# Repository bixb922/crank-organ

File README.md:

# MIDI based crank organ software and hardware

# Contents
1.  [Overview](#1-overview)
     * [How is this solution used?](#how-is-this-solution-used)
2.  [Detailed description of software and hardware, schematics, plans](#2-detailed-description-of-software-and-hardware-schematics-plans)
3.  [To see a demo](#3-to-see-a-demo)
4.  [Folders](#4-folders)
5.  [License](#5-license)
6.  [Disclaimer](#6-disclaimer)
7.  [Feedback](#7-feedback)
# 1. Overview

This animation shows how a crank organ with MIDI control works:

The crank moves the bellows. The air is pumped into a reservoir, which connects to the windchest with the pipes. A single pipe is shown, but usually a crank organ has anywhere between 15 and 100 or more pipes. Under the foot of the pipe is a electromagnetical valve (a solenoid valve). The microcontroller stores MIDI files that have the exact time each note starts and stops, and energizes the solenoid (electromagnet) through a driver (a electrical current amplifier). The solenoid opens the airflow at the foot of the pipe, air enters the pipe and vibrates, producing sound. 

Here you can see my homemade crank organ: https://www.youtube.com/@bixb922. This crank organ gave origin to the electronics and software solution in this repository. The organ has 48 pipes: 35 bourdon pipes and 13 piccolo pipes. It has a crank sensor, microphone for tuning and a touch button. It has 4 electronic registers and a button to change the playback speed. Currently I have about 500 MIDI files in the organ.

This repository has a complete hardware and software solution for these devices of mechanical music. This diagram shows how this system works:

The microcontroller stores the MIDI files with the tunes and also has a web server for the cell phone (or a tablet, or PC). On the cell phone a browser such as Chrome or Firefox is used to select the MIDI files that are going to be played. Once a setlist or a tune have been selected, the microcontroller plays the files.

Please note that you really don't need a cell phone or tablet to perform: If you define a setlist, you just turn on the microcontroller and start going. You'll only need a cell phone during performance if you want to change the order of the setlist.

No special application is needed on the cell phone. Just a standard web browser like Firefox or Chrome.

The microcontroller used is a ESP32-S3. Typical boards have about 26 pins available to manage pipes and peripherals, simplifying enormously the electronics for a 20 note organ. It also manages touch pads, counters/encoders, has lots of RAM and flash at a very low battery load, so I think it is a good choice for a microcontroller.  With the available I2C capabilities, the ESP32-S3 could manage many (hundreds?) of pipes.

The repository describes the complete solution:
* hardware schematics
* list of materials
* instructions on how to build the hardware
* complete software (open source) written in a high level language: MicroPython
* a easy installation procedure for the software (no programming skills necessary)
* ready to use configuration files for common crank organ setups

There are many places on internet to describe how to build a crank organ, how to design and cut the pipes, make bellows, windchests, etc.  That description is not part of this repository. However, I included a list of interesting links and some notes on building a MIDI crank organ here: [Buildng a crank organ](building/README.md).

Please post an github issue for any question you might have. Please star this repository if you like what you have seen.

## How is this solution used?

Once the hardware is built (see hardware plans in the doc-hardware folder), install the software, and copy your MIDI files to the microcontroller via WiFi or USB (See software documentation for detailed instructions). You can add more information such as title, genre and lyrics to the music.

You control the order of the tunes with the cell phone. You select tunes to play by tapping on them on the tunelist page on the cell phone. This is done with a very intuitive and easy to use interface using a common browser like Chrome or Firefox. Everything is done over web pages: select a tune, control setlists, configuration, etc.

There are several ways to select tunes to be played:

The creative mode: Tap on a tune on the tunelist, and turn the crank (or touch and release the touchpad) and the tune plays. Then select the next tune, etc. You stay on the tunelist page.

The very creative mode: You can tap several tunes and queue them to play one after the other.

The diligent mode: Before a performance, you can tap several tunes and organize them into a setlist on the performance page. You save the setlist on flash to be ready for the next performance. When the performance begins, you power on the microcontroller, turn the crank (or touch and release the touchpad) and the setlist plays. No need to pull out the cell phone or to push buttons.

The diligent and flexible mode: You can modify the setlist on the fly with the performance page. You can delete or skip a tune, reorder tunes, or select a new tune and move to the top of the list, according to the audience and your wishes.

The very lazy mode: Don't use your cell phone. Don't define a setlist. Turn the microcontroller on. Turn the crank or touch the touchpad. All available tunes will be shuffled randomly and played. 

# 2. Detailed description of software and hardware, schematics, plans
Main documents:

* [Description of the controller software.](doc-software/README.md)
* [Description of the controller hardware and construction plans](doc-hardware/README.md)
* [Building a crank organ](/building/README.md)

Specific documents:
* [Battery](doc-hardware/battery.md). Describes  options for a battery for a crank organ.
* [Crank sensor](doc-hardware/crank-sensor.md) with a summary [here](doc-hardware/README.md#9-crank-rotation-sensor). Describes several options to build or install a crank rotation sensor. This sensor is optional.
* [How to connect an ESP32-S3 to MIDI over serial (MIDI over 5 pin DIN plug) ](https://github.com/bixb922/umidiparser/blob/master/midi_over_serial/midi_over_serial.md). This is interesting if you want to connect this solution to a MIDI card over a serial connection (MIDI over 5 pin DIN plug)
* **NEW** [Use of RC servos to move organ valves](/doc-servo/servos.md). 

This is work in progress, but I am actively using this solution on a daily basis, so I feel it is pretty stable. Please post an issue in the "issue" section or start a discussion in this repository for questions or observations.  I'll be happy to correct any problem and will try to help if there is an issue.

# 3. To see a demo
To see this software in operation, see a demo here: https://bixb922.github.io/demo/index.html.

This demo simulates the operation of the software in this repository closely. The pages have some guidance at the beginning. There is no need to install any software on your PC.

# 4. Folders

| Folder     | Contents                             |
|------------|--------------------------------------|
|bin| Compiled binary files of the software for ESP32-S3|
|building | Description and links on how to build a crank organ |
|data| Pinout templates for 20, 26 and 31 note organs |
|design-and-development| Design details and internals | 
|doc-hardware | Description of electronic hardware |
|doc-software | Description of the crank organ software in this repository|
|doc-servos| How to build valves using RC servos |
|kicad|KiCad source files for the electronics|
|src| Full source code in MicroPython language |
|static| Web pages for the microcontroller (HTML, CSS, Javascript)   |
|tools|Some tools used during development of this software |

[Here](doc-software/README.md) is a change log, see section titled "Recent changes".

# 5. License

This material is available under the MIT license:

This license and disclaimer also covers the hardware design documents. The hardware design is part of the software published here.

Copyright (c) 2023 Hermann Paul von Borries

Permission is hereby granted, free of charge, to any person obtaining a copy
of this software and associated documentation files (the "Software"), to deal
in the Software without restriction, including without limitation the rights
to use, copy, modify, merge, publish, distribute, sublicense, and/or sell
copies of the Software, and to permit persons to whom the Software is
furnished to do so, subject to the following conditions:

The above copyright notice and this permission notice shall be included in all
copies or substantial portions of the Software.

THE SOFTWARE AND DESIGN IS PROVIDED "AS IS", WITHOUT WARRANTY OF ANY KIND, EXPRESS OR
IMPLIED, INCLUDING BUT NOT LIMITED TO THE WARRANTIES OF MERCHANTABILITY,
FITNESS FOR A PARTICULAR PURPOSE AND NONINFRINGEMENT. IN NO EVENT SHALL THE
AUTHORS OR COPYRIGHT HOLDERS BE LIABLE FOR ANY CLAIM, DAMAGES OR OTHER
LIABILITY, WHETHER IN AN ACTION OF CONTRACT, TORT OR OTHERWISE, ARISING FROM,
OUT OF OR IN CONNECTION WITH THE SOFTWARE OR THE USE OR OTHER DEALINGS IN THE
SOFTWARE.

# 6. Disclaimer

The information provided here is for general informational purposes only. All information on this repository is provided in good faith, however I make no representation or warranty of any kind, express or implied, regarding the accuracy, adequacy, validity, reliability, availability or completeness of any information in this repository. 

# 7. Feedback

Feedback is welcome. Please post questions, corrections or comments here: https://github.com/bixb922/crank-organ/discussions

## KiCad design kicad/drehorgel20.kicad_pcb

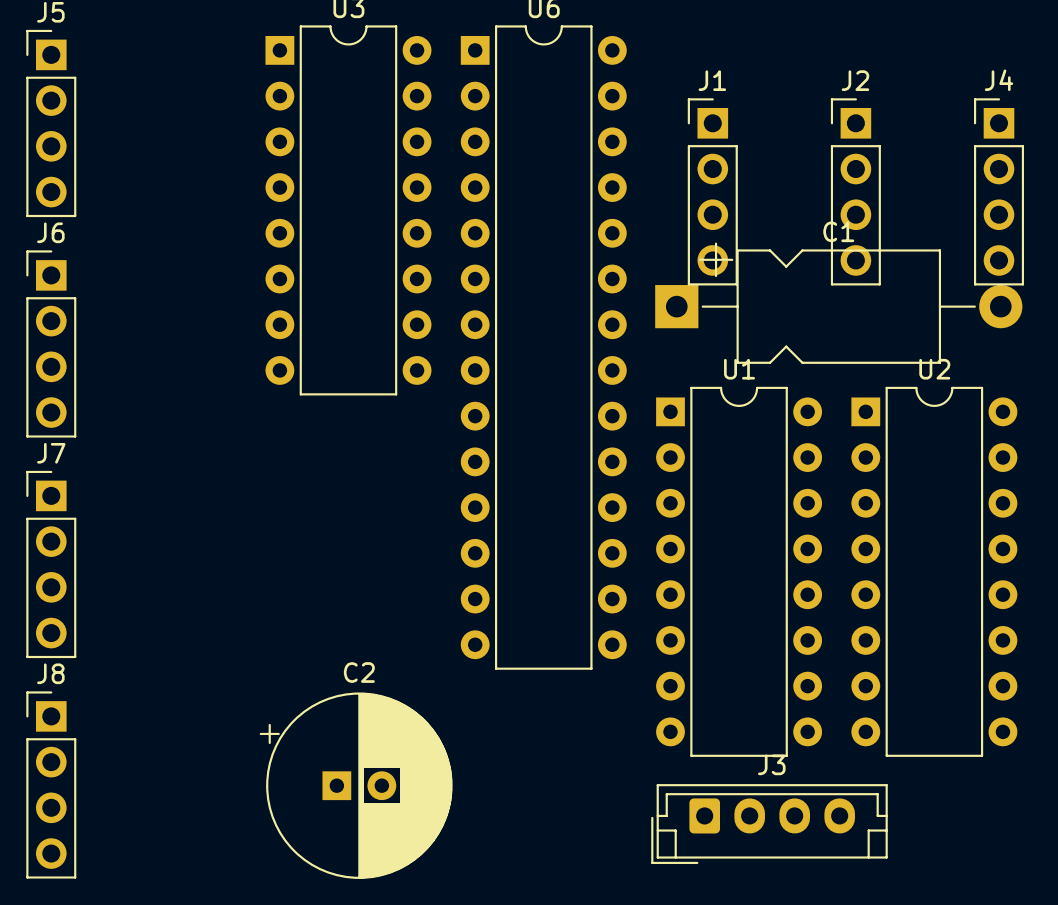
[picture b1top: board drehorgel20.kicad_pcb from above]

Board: 2 copper layers, 14 parts (0 on the bottom side), 45 nets, no tracks yet.

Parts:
C1: 100 nF; CP_Axial_L11.0mm_D6.0mm_P18.00mm_Horizontal
C2: 10uF; CP_Radial_D10.0mm_P2.50mm
J1: I2C; PinHeader_1x04_P2.54mm_Vertical
J2: GPIO; PinHeader_1x04_P2.54mm_Vertical
J3: Power; JST_EH_B4B-EH-A_1x04_P2.50mm_Vertical
J4: Solenoid-1; PinHeader_1x04_P2.54mm_Vertical
J5: Solenoid-2; PinHeader_1x04_P2.54mm_Vertical
J6: Solenoid-3; PinHeader_1x04_P2.54mm_Vertical
J7: Solenoid-4; PinHeader_1x04_P2.54mm_Vertical
J8: Solenoid-5; PinHeader_1x04_P2.54mm_Vertical
U1, U2, U3: ULN2003A; DIP-16_W7.62mm
U6: MCP23017_SP; DIP-28_W7.62mm

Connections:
12V: C1.1, C2.1, J3.1, J3.2, U1.9 (COM), U2.9 (COM), U3.9 (COM)
GND: C1.2, C2.2, J1.3, J3.3, U1.8 (GND), U2.8 (GND), U3.8 (GND), U6.10 (VSS), U6.15 (A0), U6.16 (A1), U6.17 (A2)
unnamed: J1.1, U6.13 (SDA)
unnamed: J1.2, U6.12 (SCK)
unnamed: J2.1, U3.1 (I1)
unnamed: J2.2, U3.2 (I2)
unnamed: J2.3, U3.3 (I3)
unnamed: J2.4, U3.4 (I4)
unnamed: J4.1, U3.16 (O1)
unnamed: J4.2, U3.15 (O2)
unnamed: J4.3, U3.14 (O3)
unnamed: J4.4, U3.13 (O4)
unnamed: J5.1, U3.11 (O6)
unnamed: J5.2, U3.10 (O7)
unnamed: J5.3, U2.16 (O1)
unnamed: J5.4, U2.15 (O2)
unnamed: J6.1, U2.14 (O3)
unnamed: J6.2, U2.13 (O4)
unnamed: J6.3, U2.12 (O5)
unnamed: J6.4, U2.11 (O6)
unnamed: J7.1, U2.10 (O7)
unnamed: J7.2, U1.16 (O1)
unnamed: J7.3, U1.15 (O2)
unnamed: J7.4, U1.14 (O3)
unnamed: J8.1, U1.13 (O4)
unnamed: J8.2, U1.12 (O5)
unnamed: J8.3, U1.11 (O6)
unnamed: J8.4, U1.10 (O7)
unnamed: U1.1 (I1), U6.22 (GPA1)
unnamed: U1.2 (I2), U6.23 (GPA2)
unnamed: U1.3 (I3), U6.24 (GPA3)
unnamed: U1.4 (I4), U6.25 (GPA4)
unnamed: U1.5 (I5), U6.26 (GPA5)
unnamed: U1.6 (I6), U6.27 (GPA6)
unnamed: U1.7 (I7), U6.28 (GPA7)
unnamed: U2.1 (I1), U6.3 (GPB2)
unnamed: U2.2 (I2), U6.4 (GPB3)
unnamed: U2.3 (I3), U6.5 (GPB4)
unnamed: U2.4 (I4), U6.6 (GPB5)
unnamed: U2.5 (I5), U6.7 (GPB6)
unnamed: U2.6 (I6), U6.8 (GPB7)
unnamed: U2.7 (I7), U6.21 (GPA0)
unnamed: U3.6 (I6), U6.1 (GPB0)
unnamed: U3.7 (I7), U6.2 (GPB1)
Vcc 3.3V: J1.4, U6.9 (VDD), U6.18 (~RESET)

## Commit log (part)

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2023-09-29 Initial file upload
2023-10-03 Now maximum amplitude for 0dB amplitude is calculated
2023-10-03 renamed md files to README
2023-10-03 added folder table to README.md
2023-10-03 Corrected table README.md
2023-10-03 Complete the documentation, overview, hardware, photos
2023-10-03 Update tunelib documentation
2023-10-03 corrected RADME.md
2023-10-03 Clarify how to start a waiting tune
2023-10-03 Reorganized description of 12V to ESP32-S3
2023-10-05 Optimized setlist response time. Automated initial config.json completely
2023-10-05 Optimized setlist response time. Automatic creation of config.json
2023-10-05 Updated hardware license
2023-10-05 Corrected tunlist image
2023-10-05 More photos on hardware description. Deleted log debug option on config.html
2023-10-05 Better validation when config.json data is changed
2023-10-06 Moved data files to data folder.
2023-10-06 Added comments
2023-10-07 Added germantranslation. Added comments. Added install.py for easy installation. Added missing files.
2023-10-08 Added more copyright and credits
2023-11-07 New version, many changes
2023-11-07 Updated software documentation. Added change list.
2023-11-07 Updated list of software changes
2023-11-07 Test mermaid diagrams
2023-11-07 Test mermaid diagrams 2
2023-11-07 Corrected mermaid syntax for github
2023-11-07 Added missing image
2023-11-07 Updated software documentation with operation of time zones
2023-11-07 Updated documentation. Deleted some debug messages
2023-11-07 Updated descriptions
2023-11-07 Smaller images
2023-11-08 Corrected bug using wrong units for sleep
2023-11-08 Heartbeat config. Web authentication adapted to Microdot
2023-11-09 Add more info to battery status. Update mmd to mermaid tags in diagrams for github
2023-11-09 Updated software documentation
2023-11-13 Hardware doc. Software: see change list in readme
2023-11-15 Add salt for password encryption. Button to purge old history
2023-11-15 Install files for german and spanish language support
2023-11-18 FTP button is now on index page
2023-11-19 Better intro, new diagram of crank-organ
2023-11-20 Update main README
2023-11-20 Clarified documentation
2023-11-25 working on generalizing html
2024-01-05 ruff formatting. Rewrote led.py. Server support. Fixes
2024-01-05 Update 'fast install' scripts
2024-01-09 Optimized code, more led colors, better search of MIDIdict object
2024-01-09 More consistent names (tunelib), use repr(exception) to see complete description
2024-01-10 Update installation instructions. Update installation files
2024-01-15 Rewrote tachometer module. Structure tachometer/touchpad/setlist with asyncio events. Use fileops in timezone module
2024-02-20 New tuner with FFT. New gauge widgets. Delay queries to NTP server. Many glitches corrected
2024-02-20 Updated installation kit, english, spanish and german
2024-02-20 Updated readme introduction
2024-02-20 Improved link to description, updated software readme
2024-02-20 Updated readme and simplified color scheme in CSS
2024-03-13 Updated to latest Microdot. New design of graphic bars. Check surplus items in config. Initialize .json files if not present. Save microphone signal. Streamline startup. aioprof done.
2024-03-13 Add context manager to show exexecution time
2024-03-13 Cleanup of change from history.db to history.json
2024-03-16 Code cleanup after using ruff
2024-03-16 Better documentation of fft parameters. Corrected note.html. Code cleanup
2024-03-24 Automate battery calibration. Automatic playback. Tune FFT parameters. Make saving signals configurable
2024-03-24 Update software README with new features
2024-03-25 Corrected false start of melody due to RPS change
2024-03-27 Deleted obsolete code. Better battery calibration, don't show if not done. Show buttons during automatic playback
2024-03-27 Timezone could result in 0 if error in web service
2024-03-27 Timezone set to 0 corrected. Battery estimate_low corrected
2024-04-03 FTP as last resort action. Use RTC to set local time. Log webserver times. Don't revoke authorization each time. Cleanup old code. Handle exception if signal folder empty
2024-04-12 Register rating and comments. Automatically refresh tunelib
2024-04-12 Make double touch either stop current tune or shuffle all
2024-04-12 Sort history on descending date
2024-04-14 Clean up comments
2024-04-14 Clean up code, add comments
2024-04-28 Led blinking when setlist empty. More comments
2024-04-28 More comments in code
2024-04-30 Tachometer and crank. Tempo follows crank option on play.html page
2024-05-21 Lyrics support. Streamlined code. Bug fixes. More configurable crank settings. Info field in tunelist now clickable for detail. Search tunelist for rating.
2024-05-23 Updated translated files. Optimizations.
2024-05-24 Tune lib page allows to show grid for copy/paste to spreadsheet
2024-06-25 New Pulse Driver module using hardware PCNT module. RPS graph on diag.html page. Unify LED colors, Add from micropython import const for linter. Rewrote event handling related to crank. Description i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
2024-06-25 Updated installation packages
2024-06-25 New installation, no separate language files
2024-06-25 Add empty configuration files
2024-06-25 Update installation files
2024-06-25 Updated installation and README
2024-06-25 Added kicad files for 20 note organ
2024-06-25 Update README with change log
2024-06-26 Update documentation. Don't create lyrics folder
2024-06-26 Updated README. Removed 'initial page' option
2024-08-24 Battery tutorial
2024-10-09 File manager. Drum sounds. Registers. Many smaller improvements, see software README
2024-10-30 Added support for quadrature encoder, midi over serial, automatic time zone detection, rotary actuator
2025-01-06 Fixed test MCP wrong MCP address, and wrong SCL/SDA PIN numbers
    On pinout.html , if there are multiple MCPs defined, the MCP address and SCL/SDA always pointed to the last MCP.
2025-01-10 MIDI file compression. Crank smoothing. Smaller code
2025-01-12 Corrected pinout.json files. Many optimizations
2025-01-16 Corrected several bugs
2025-01-19 Streamlined setlist processing if empty. Applied pylance with MicroPython stubs and corrected errors
2025-01-23 2 buttons on index page. Corrected bugs
2025-01-24 Add table of contents to .md files
2025-01-29 Documentation and comments. Linter corrections
2025-01-29 Updated main readme with links to documents
2025-01-29 Updated .gitignore
2025-01-29 Updated crank sensor info
2025-01-29 Updated documentation
2025-01-29 Fixed links in documentation
2025-01-29 Fixed documentation links
2025-01-31 Update compress_midi.py, add time=delta to program changes
2025-02-25 Corrected bugs in setlist.top. compare_midi.py: corrected time calculations, added bass correction, added compare with tunelib.json.
2025-03-04 Documented changes
2025-03-05 Correct umidiparser regression
2025-03-28 Tuning statistics, tuning parameters, bug fixes
2025-03-28 MIDI numbering is now 1-16 on pinout page instead of 0-15
2025-04-07 Pace downloads. Red blink bug. NFC file name normalization revisited. Documentation.
2025-04-07 Update hardware doc with reference to MIDI over serial
2025-04-07 Add MIDI over serial link to hardware description
2025-05-07 Background tunelib update. Bug fixes. Stability
2025-05-09 Correct bug in tunemanager that analyzed files even when not needed
2025-05-09 Update documentation for design and development
2025-05-09 Update documentation
2025-05-28 Match note on/off. Streamline tunelib update. Configure mic for amplitude. Some enhancements and optimizations
2025-06-14 Complete test buttons. Notes on building. Experimental RC servo driver
2025-06-23 PCA9685 servo motor support
2025-07-04 RC servos
2025-07-04 Update contants of doc
2025-07-05 Update docs
2025-07-06 Improve docs
2025-10-28 Multiple setlists and many other changes Jul 6, 2025 to Oct 28, 2025
2026-04-06 Many fixes, enhancements and optimizations
2026-04-06 Update comments
2026-04-07 Update docs. Link doc about building a crank organ
2026-04-11 Use MicroPython 1.28.0. Some fixes
2026-04-13 Update battery.md, tool battery section
2026-04-18 Freeze main.py, boot.py. I2C and mic test buttons
2026-04-18 Touchpad test on pinout page
2026-04-19 Update docs. Enhance Test button functionality on pinout page
2026-04-24 Device not found is now error, not exception
2026-04-25 Add color to html log too
2026-04-25 Add universal folder
2026-05-12 Improve crank driver. Make startup more resilient
2026-05-19 Reduce RAM footprint. Rework bin image generation
2026-05-19 Updated docs
2026-05-20 Add barrel mode to play page, move tempo follows crank next to barrel mode checkbox
2026-05-27 Replace barrel mode with repeat requested option. Handle overlapping MIDI events better in compress_midi.py utility
2026-06-08 Implement switch as alternative to touch pad. Restore the rotary encoder to change tempo. Update docs
